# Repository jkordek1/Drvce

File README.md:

# Christmas tree

## What is it?
Christmas tree powered by ATTiny85 microcontroller. WS2812-B (neopixel) LEDs with automatic brightness control which adapt to the lighting conditions.

## YouTube
See it in action: https://www.youtube.com/watch?v=5eK83JGs8PI

## Images

## Project folder structure
    .
    ├── ...
    ├── Images                  # Images of the project
    ├── Output files            # Gerber files
    ├── KiCadFiles              # Main folder
    │   ├── assembly            # Assembly files
    │   ├── bom                 # ibom assembly files
    │   └── gerber              # gerber
    ├── Schematic.pdf           # Schematic .pdf file
    └── ...

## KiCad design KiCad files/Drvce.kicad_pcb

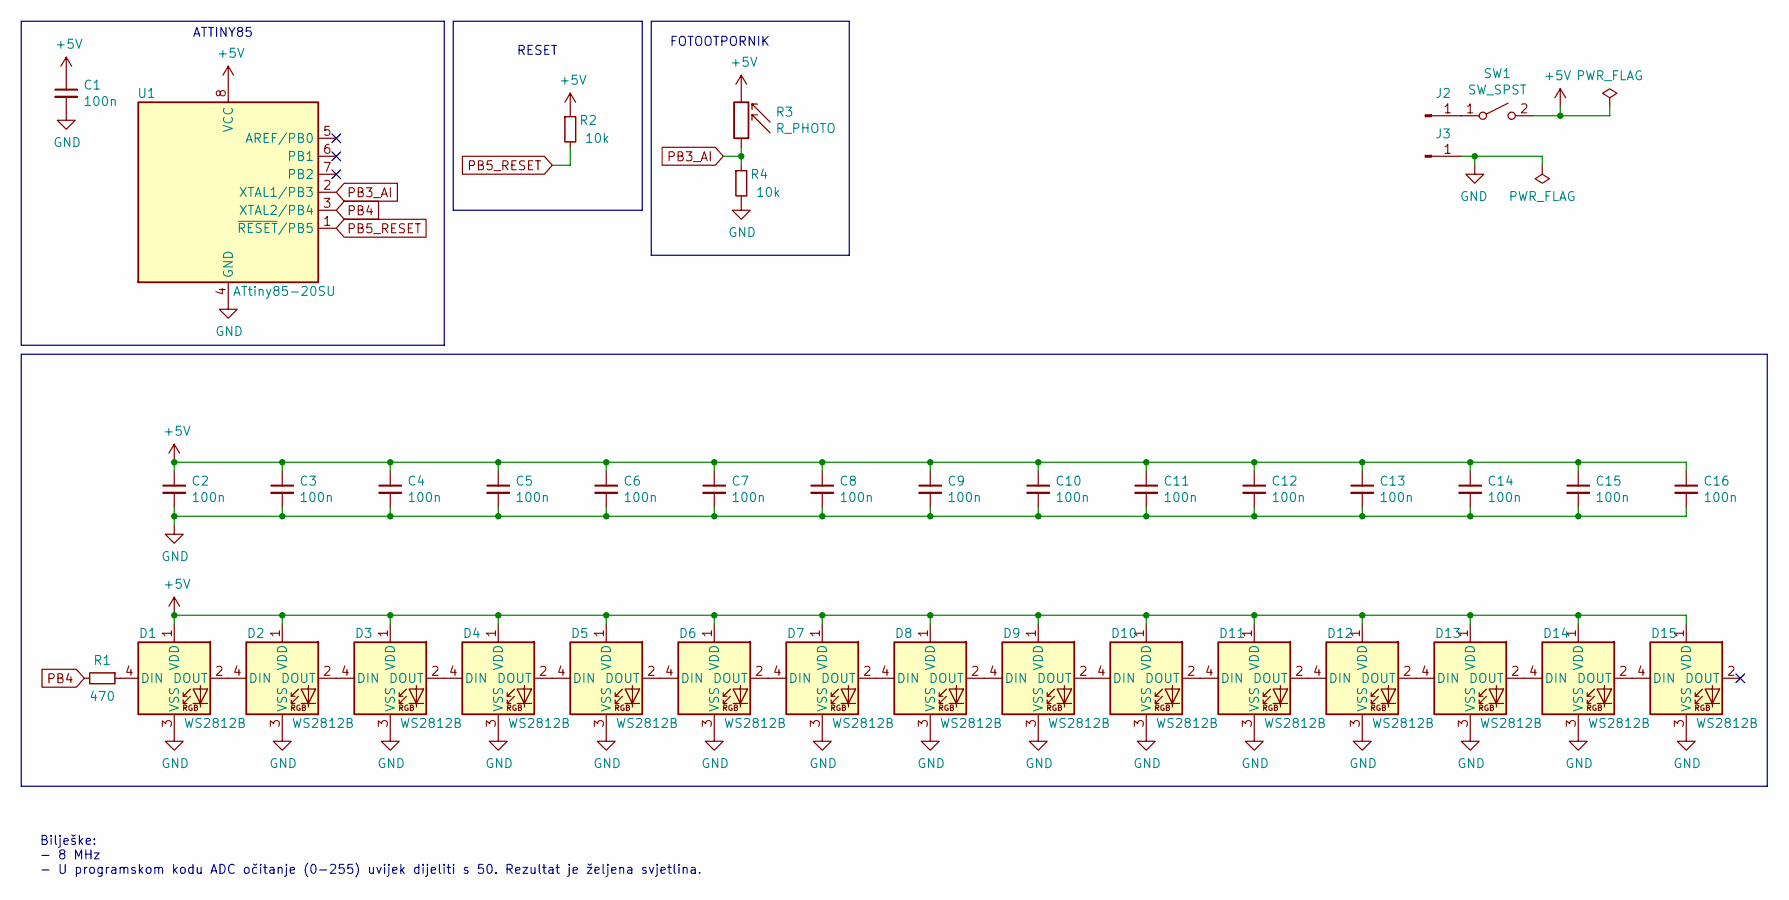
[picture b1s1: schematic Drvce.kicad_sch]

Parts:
C1, C2, C3, C4, C5, C6, C7, C8, C9, C10, C11, C12, C13, C14, C15, C16: 100n; C_0603_1608Metric; LCSC Part # C14663
D1, D2, D3, D4, D5, D6, D7, D8, D9, D10, D11, D12, D13, D14, D15: WS2812B; LED_WS2812B_edited; LCSC Part # C114587
J2: +; SolderWirePad_1x01_SMD_5x10mm
J3: -; SolderWirePad_1x01_SMD_5x10mm
R1: 470; R_0603_1608Metric; LCSC Part # C23179
R2, R4: 10k; R_0603_1608Metric; LCSC Part # C25804
R3: R_PHOTO; R_LDR_5.1x4.3mm_P3.4mm_Vertical_edited
SW1: SW_SPST; SW_SPDT_PCM12
U1: ATtiny85-20SU; SOIJ-8_5.3x5.3mm_P1.27mm; LCSC Part # C89852

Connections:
+5V: C1.1, C2.1, C3.1, C4.1, C5.1, C6.1, C7.1, C8.1, C9.1, C10.1, C11.1, C12.1, C13.1, C14.1, C15.1, C16.1, D1.1 (VDD), D2.1 (VDD), D3.1 (VDD), D4.1 (VDD), D5.1 (VDD), D6.1 (VDD), D7.1 (VDD), D8.1 (VDD), D9.1 (VDD), D10.1 (VDD), D11.1 (VDD), D12.1 (VDD), D13.1 (VDD), D14.1 (VDD), D15.1 (VDD), R2.1, R3.2, SW1.2 (B), U1.8 (VCC)
GND: C1.2, C2.2, C3.2, C4.2, C5.2, C6.2, C7.2, C8.2, C9.2, C10.2, C11.2, C12.2, C13.2, C14.2, C15.2, C16.2, D1.3 (VSS), D2.3 (VSS), D3.3 (VSS), D4.3 (VSS), D5.3 (VSS), D6.3 (VSS), D7.3 (VSS), D8.3 (VSS), D9.3 (VSS), D10.3 (VSS), D11.3 (VSS), D12.3 (VSS), D13.3 (VSS), D14.3 (VSS), D15.3 (VSS), J3.1, R4.2, U1.4 (GND)
unnamed: D1.2 (DOUT), D2.4 (DIN)
unnamed: D1.4 (DIN), R1.1
unnamed: D2.2 (DOUT), D3.4 (DIN)
unnamed: D3.2 (DOUT), D4.4 (DIN)
unnamed: D4.2 (DOUT), D5.4 (DIN)
unnamed: D5.2 (DOUT), D6.4 (DIN)
unnamed: D6.2 (DOUT), D7.4 (DIN)
unnamed: D7.2 (DOUT), D8.4 (DIN)
unnamed: D8.2 (DOUT), D9.4 (DIN)
unnamed: D10.2 (DOUT), D11.4 (DIN)
unnamed: D9.2 (DOUT), D10.4 (DIN)
unnamed: D11.2 (DOUT), D12.4 (DIN)
unnamed: D12.2 (DOUT), D13.4 (DIN)
unnamed: D13.2 (DOUT), D14.4 (DIN)
unnamed: D14.2 (DOUT), D15.4 (DIN)
unnamed: J2.1, SW1.1 (A)
PB3_AI: R3.1, R4.1, U1.2 (XTAL1/PB3)
PB4: R1.2, U1.3 (XTAL2/PB4)
PB5_RESET: R2.2, U1.1 (~RESET/PB5)

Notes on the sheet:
Bilješke: - 8 MHz - U programskom kodu ADC očitanje (0-255) uvijek dijeliti s 50. Rezultat je željena svjetlina.
FOTOOTPORNIK
RESET
ATTINY85

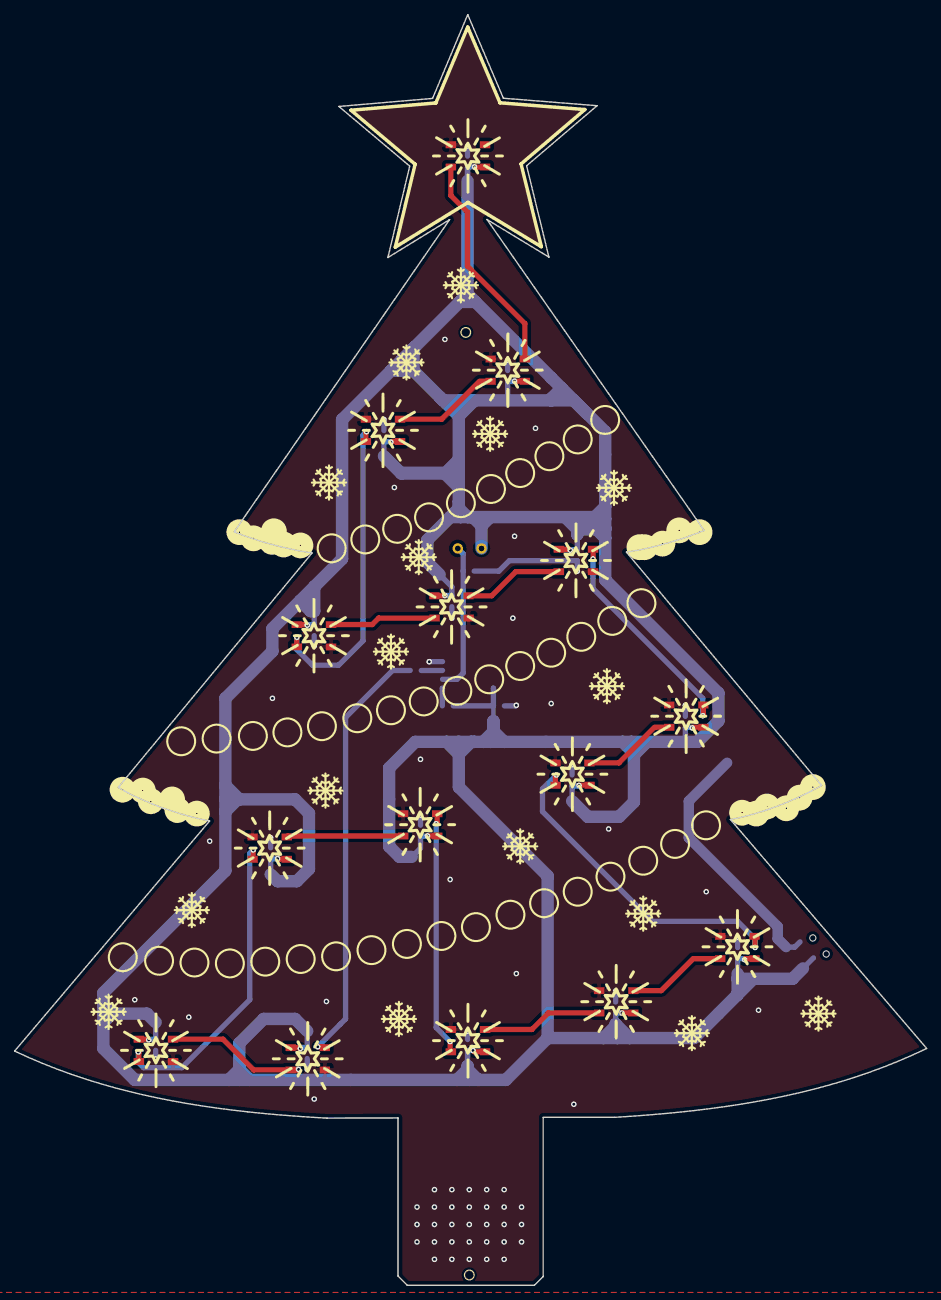
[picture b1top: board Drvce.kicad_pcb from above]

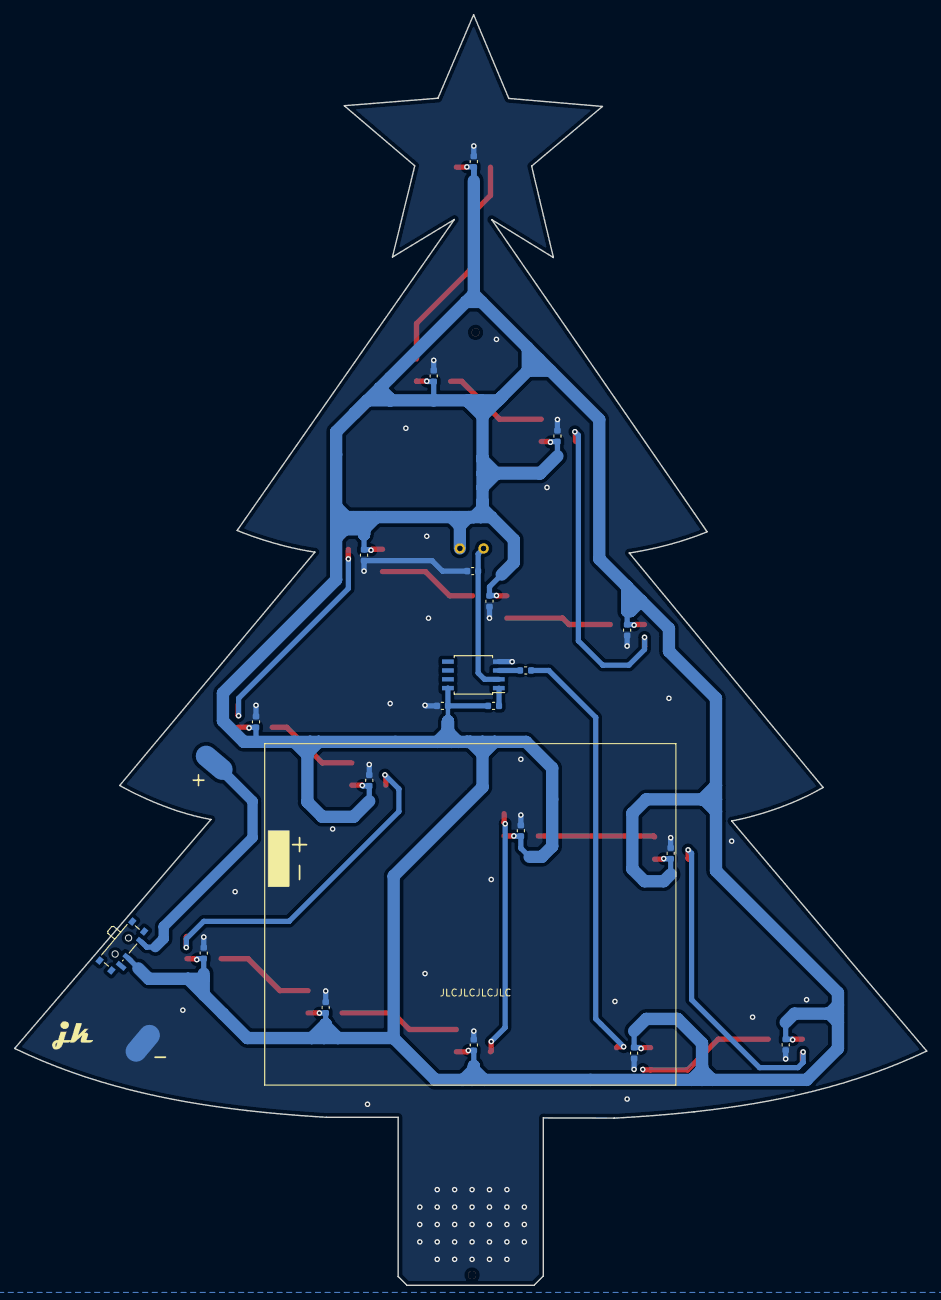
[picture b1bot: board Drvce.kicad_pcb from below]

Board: 2 copper layers, 130.9 x 182.3 mm, 39 parts (23 on the bottom side), 21 nets.

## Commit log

2022-02-09 Inital
2022-02-09 assembly
2022-02-09 Images
